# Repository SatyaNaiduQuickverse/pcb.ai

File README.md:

# PCB project starter kit

This repo is the working base for a **Claude-driven PCB design project**, run with a
**master / worker** pair of Claude sessions plus a human project owner.

It is a *starter kit* — it carries the rules, the rigor discipline, the master/worker
protocol, the PCB design-phase structure, and the hard-won lessons from a prior
project. It does **not** yet contain a specific PCB. The project owner briefs the
master on what the board is; the master records it in `CLAUDE.md §2` and the work
begins.

## Read order (cold start)

1. `CLAUDE.md` — the bootstrap: the master/worker model, the rules, the working style.
2. `docs/ENGINEERING_RIGOR.md` — the non-negotiable commitments.
3. `docs/MASTER_WORKER_PROTOCOL.md` — how master and worker communicate + coordinate.
4. `docs/NOVA_COORD_SETUP.md` — deploying this project's coordination server.
5. `docs/DESIGN_PHASES.md` — the PCB design-phase structure (the canonical plan).
6. `docs/PCB_PLAYBOOK.md` — the toolchain + the hard-won routing / manufacturability / sim lessons.

## The model in one line

The **project owner** sets direction. The **master** orchestrates, reviews, gates, and
adjudicates. The **worker** executes the hands-on work (KiCad, sims, builds, fab files).
Master and worker each run as a Claude session; they talk over a small coordination
server. Every phase passes a verification gate before the next begins.

## First steps for a new project

1. Project owner briefs the master on the PCB (function, interfaces, constraints).
2. Master records the project identity + system context in `CLAUDE.md §2` and writes
   a project-specific interface/requirements doc.
3. Master + worker stand up the toolchain and the coordination channel
   (`docs/MASTER_WORKER_PROTOCOL.md`).
4. Work proceeds phase by phase per `docs/DESIGN_PHASES.md`, gated.

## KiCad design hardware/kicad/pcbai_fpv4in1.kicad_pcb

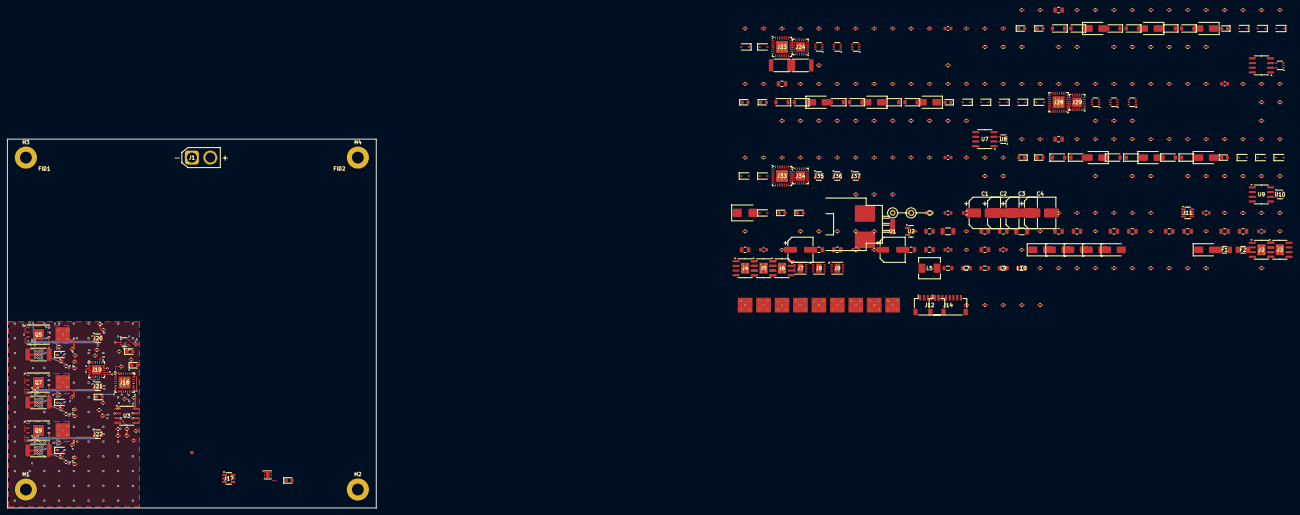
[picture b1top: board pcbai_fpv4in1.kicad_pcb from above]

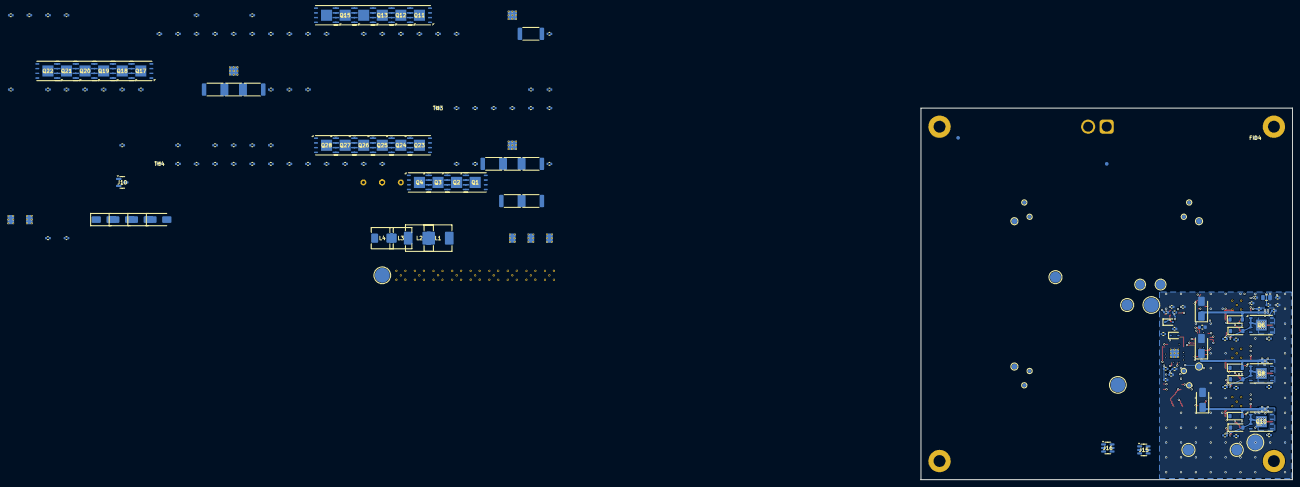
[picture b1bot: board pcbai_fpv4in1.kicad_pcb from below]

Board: 10 copper layers, 100.0 x 100.0 mm, 573 parts (175 on the bottom side), 260 nets.

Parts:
C1, C2, C3, C4: EEHZS1V471P_470uF_35V_polymer; CP_Elec_8x6.2
C5, C9, C13, C16, C19, C53, C83, C113, C143: 10uF; C_0805_2012Metric
C6, C10: 22uF; C_1206_3216Metric
C7, C11, C14, C17, C20, C24, C27, C32, C37, C40, C41, C43, C48, C49, C50, C51, C52, C54, C56, C58, C62, C65, C68, C71, C72, C73, C79, C80, C81, C82, C84, C86, C88, C92, C95, C98, C101, C102, C103, C109, C110, C111, C112, C114, C116, C118, C122, C125, C128, C131, C132, C133, C139, C140, C141, C142, C144, C146, C148, C152, C155, C158, C161, C162, C163, C169, C170: 100nF; C_0402_1005Metric
C8, C12, C15, C18, C21, C22, C25, C29, C30, C34, C35, C38: 22uF; C_0805_2012Metric
C23, C26, C31, C36, C39: 10uF; C_0603_1608Metric
C28, C33: 100uF_6V3_polymer; CP_Elec_6.3x7.7
C42, C45, C46, C47, C55, C57, C59, C60, C61, C85, C87, C89, C90, C91, C115, C117, C119, C120, C121, C145, C147, C149, C150, C151: 1uF; C_0402_1005Metric
C44, C63, C66, C69, C78, C93, C96, C99, C108, C123, C126, C129, C138, C153, C156, C159, C168: 10nF; C_0402_1005Metric
C64, C67, C70, C74, C75, C76, C94, C97, C100, C104, C105, C106, C124, C127, C130, C134, C135, C136, C154, C157, C160, C164, C165, C166: 1nF; C_0402_1005Metric
C77, C107, C137, C167: 22uF; C_0603_1608Metric
D1: SMBJ33A; D_SMB
D2: 12V; D_SOD-323
D3: GREEN_PWR; LED_0603_1608Metric
D4: RED_RPOL; LED_0603_1608Metric
D5, D6, D7, D8, D9: SS54; D_SMA
D10, D11, D12: SMAJ5.0A; D_SMA
D13, D14: SMAJ9.0A; D_SMA
D15, D16, D17, D18: RED_KILL_FW; LED_0603_1608Metric
D19, D20, D21, D22: RED_FAULT_HW; LED_0603_1608Metric
D23: GREEN; LED_0603_1608Metric
D24, D25, D27, D28, D30, D31, D39, D40, D42, D43, D45, D46, D54, D55, D57, D58, D60, D61, D69, D70, D72, D73, D75, D76: BZT52C5V6; D_SOD-123
D26, D29, D32, D41, D44, D47, D56, D59, D62, D71, D74, D77: SMBJ33A; D_SMA
D33, D48, D63, D78: RED; LED_0603_1608Metric
D34, D35, D36, D37, D38, D49, D50, D51, D52, D53, D64, D65, D66, D67, D68, D79, D80, D81, D82, D83: BAT54; D_SOD-323
F1, F2: MF-MSMF200; Fuse_1206_3216Metric
FID1, FID2, FID3, FID4, FID5, FID6: Fiducial_1mm_Mask2mm
H1, H2, H3, H4: MountingHole; MountingHole_3.2mm_M3
J1: BATT_PAD; AMASS_XT30U-M_1x02_P5.0mm_Vertical
J2, J3, J4: TPS54560DDAR; SOIC-8-1EP_3.9x4.9mm_P1.27mm_EP2.29x3mm_ThermalVias
J5, J6: AOZ1284PI; SOIC-8-1EP_3.9x4.9mm_P1.27mm_EP2.29x3mm_ThermalVias
J7, J8, J9: TPS259251DRCR; DFN-10-1EP_3x3mm_P0.5mm_EP1.55x2.48mm
J10: VSUP_5V_TBD; SOT-23
J11: TPS3700_VMOTOR_27V_18V; SOT-23-8
J12: BM06B-SRSS-TB; JST_SH_SM06B-SRSS-TB_1x06-1MP_P1.00mm_Horizontal
J13: TLV76733DRVR; WSON-6-1EP_2x2mm_P0.65mm_EP1x1.6mm
J14: SM08B-SRSS-TB; JST_SH_SM08B-SRSS-TB_1x08-1MP_P1.00mm_Horizontal
J15, J16, J17: USBLC6-2SC6; SOT-23-6
J18, J23, J28, J33: AT32F421K8U7; QFN-32-1EP_5x5mm_P0.5mm_EP3.3x3.3mm_ThermalVias
J19, J24, J29, J34: DRV8300DRGER; HVQFN-24-1EP_4x4mm_P0.5mm_EP2.6x2.6mm
J20, J21, J22, J25, J26, J27, J30, J31, J32, J35, J36, J37: INA186A3IDCKR; SOT-363_SC-70-6
L1, L2: 4.7uH; L_Sunlord_MWSA0605S
L3: 8.2uH; L_Sunlord_MWSA0503S
L4, L5: 10uH; L_Sunlord_MWSA0503S
L6, L7, L8, L9, L10: 600ohm@100MHz; L_0805_2012Metric
L11: 120ohm@100MHz; L_0201_0603Metric
Q1, Q2, Q3, Q4, Q5, Q6, Q7, Q8, Q9, Q10, Q11, Q12, Q13, Q14, Q15, Q16, Q17, Q18, Q19, Q20, Q21, Q22, Q23, Q24, Q25, Q26, Q27, Q28: BSC014N06NS; W-PDFN-8-1EP_6x5mm_P1.27mm_EP3x3mm
R1, R2: MF72_5D25; R_Axial_DIN0207_L6.3mm_D2.5mm_P5.08mm_Vertical
R3: 10K; R_0603_1608Metric
R4, R5: 5K1; R_0603_1608Metric
R6, R8, R10: 52K3; R_0402_1005Metric
R7, R9, R11, R13, R15, R16, R17, R18, R21, R31, R40, R41, R42, R43, R47, R48, R51, R52, R55, R56, R67, R73, R74, R76, R77, R78, R79, R83, R84, R87, R88, R91, R92, R103, R109, R110, R112, R113, R114, R115, R119, R120, R123, R124, R127, R128, R139, R145, R146, R148, R149, R150, R151, R155, R156, R159, R160, R163, R164, R175, R181, R182, R184: 10K; R_0402_1005Metric
R12, R14: 102K; R_0402_1005Metric
R19: 348K; R_0603_1608Metric
R20: 23K2; R_0402_1005Metric
R22, R23, R24, R25, R26, R27, R28, R29, R35, R66, R68, R102, R104, R138, R140, R174, R176: 1K; R_0402_1005Metric
R30: 0R; R_0402_1005Metric
R32, R75, R111, R147, R183: 20K; R_0402_1005Metric
R33, R34: 0R; R_2512_6332Metric
R36, R38, R72, R108, R144, R180: 100K; R_0402_1005Metric
R37: 14K; R_0402_1005Metric
R39: 390R; R_0402_1005Metric
R44, R80, R116, R152: 40K; R_0402_1005Metric
R45, R46, R49, R50, R53, R54, R81, R82, R85, R86, R89, R90, R117, R118, R121, R122, R125, R126, R153, R154, R157, R158, R161, R162: 15R; R_0402_1005Metric
R57, R58, R59, R93, R94, R95, R129, R130, R131, R165, R166, R167: 0.2mR; R_2512_6332Metric
R60, R62, R64, R70, R96, R98, R100, R106, R132, R134, R136, R142, R168, R170, R172, R178: 22K; R_0402_1005Metric
R61, R63, R65, R97, R99, R101, R133, R135, R137, R169, R171, R173: 3.3K; R_0402_1005Metric
R69, R105, R141, R177: 24K; R_0402_1005Metric
R71, R107, R143, R179: 3K; R_0402_1005Metric
TH1, TH2, TH3, TH4: 10K_B4250; R_0402_1005Metric
TP1: PAD_V5_FC_PLUS; TestPoint_Pad_D4.0mm
TP2: PAD_V5_FC_GND; TestPoint_Pad_D4.0mm
TP3: PAD_V5_PI5_PLUS; TestPoint_Pad_D4.0mm
TP5: PAD_V5_AI_PLUS; TestPoint_Pad_D4.0mm
TP7: PAD_V9_VTX1_PLUS; TestPoint_Pad_D3.0mm
TP9: PAD_V9_VTX2_PLUS; TestPoint_Pad_D3.0mm
TP10: PAD_V9_VTX2_GND; TestPoint_Pad_D3.0mm
TP11: PAD_V3V3_PLUS; TestPoint_Pad_D2.5mm
TP12: PAD_V3V3_GND; TestPoint_Pad_D2.5mm
TP16: PAD_GND_DIST_4; TestPoint_Pad_D3.0mm
TP17: BOOT_JUMPER_CH1; TestPoint_Pad_D1.5mm
TP19: MOTOR_A_CH1; ESCMotorPad_4x4mm_5via
TP20: MOTOR_B_CH1; ESCMotorPad_4x4mm_5via
TP21: MOTOR_C_CH1; ESCMotorPad_4x4mm_5via
TP22: SWDIO_CH1; TestPoint_Pad_D1.0mm
TP23: SWCLK_CH1; TestPoint_Pad_D1.0mm
TP24: BOOT_JUMPER_CH2; TestPoint_Pad_D1.5mm
TP26: MOTOR_A_CH2; ESCMotorPad_4x4mm_5via
TP27: MOTOR_B_CH2; ESCMotorPad_4x4mm_5via
TP28: MOTOR_C_CH2; ESCMotorPad_4x4mm_5via
TP29: SWDIO_CH2; TestPoint_Pad_D1.0mm
TP30: SWCLK_CH2; TestPoint_Pad_D1.0mm
TP31: BOOT_JUMPER_CH3; TestPoint_Pad_D1.5mm
TP33: MOTOR_A_CH3; ESCMotorPad_4x4mm_5via
TP34: MOTOR_B_CH3; ESCMotorPad_4x4mm_5via
TP35: MOTOR_C_CH3; ESCMotorPad_4x4mm_5via
TP36: SWDIO_CH3; TestPoint_Pad_D1.0mm
TP37: SWCLK_CH3; TestPoint_Pad_D1.0mm
TP38: BOOT_JUMPER_CH4; TestPoint_Pad_D1.5mm
TP40: MOTOR_A_CH4; ESCMotorPad_4x4mm_5via
TP41: MOTOR_B_CH4; ESCMotorPad_4x4mm_5via
TP42: MOTOR_C_CH4; ESCMotorPad_4x4mm_5via
TP43: SWDIO_CH4; TestPoint_Pad_D1.0mm
TP44: SWCLK_CH4; TestPoint_Pad_D1.0mm
U1: ACS770ECB-200B-PFF-T; Allegro_CB_PFF
U2: TL431LI; SOT-23
U3, U5, U7, U9: LM393; SOIC-8_3.9x4.9mm_P1.27mm
U4, U6, U8, U10: 74LVC1G08; SOT-353_SC-70-5

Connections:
+3V3: C46.1, C51.1, C52.1, C53.1, C79.1, C80.1, C81.1, C82.1, C83.1, C109.1, C110.1, C111.1, C112.1, C113.1, C139.1, C140.1, C141.1, C142.1, C143.1, C169.1, C170.1, J11.1, J11.7, J11.8, J12.2, J13.5, J18.1, J18.17, J20.4, J21.4, J22.4, J23.1, J23.17, J25.4, J26.4, J27.4, J28.1, J28.17, J30.4, J31.4, J32.4, J33.1, J33.17, J35.4, J36.4, J37.4, L11.1, R21.2, R22.1, R23.1, R24.1, R25.1, R26.1, R27.1, R28.1, R29.1, R35.1, R39.1, R40.2, R42.2, R66.1, R67.1, R73.2, R74.2, R76.2, R78.2, R102.1, R103.1, R109.2, R110.2, R112.2, R114.2, R138.1, R139.1, R145.2, R146.2, R148.2, R150.2, R174.1, R175.1, R181.2, R182.2, R184.2, TP11.1, U3.8, U4.5, U5.8, U6.5, U7.8, U8.5, U9.8, U10.5
+3V3A: C47.1, C48.1, C54.1, C55.1, C84.1, C85.1, C114.1, C115.1, C144.1, C145.1, J18.5, J23.5, J28.5, J33.5, L11.2
+BATT: J1.1, R1.1, R2.1, R5.1, R36.1
+V5_AI: C30.1, C31.1, C32.1, C33.1, C34.1, L8.2, TP5.1
+V5_FC: C22.1, C23.1, C24.1, C45.1, C57.1, C58.1, C77.1, C87.1, C88.1, C107.1, C117.1, C118.1, C137.1, C147.1, C148.1, C167.1, J13.1, J13.3, J15.3, J16.3, J17.3, J19.4, J24.4, J29.4, J34.4, L6.2, R30.1, TP1.1
+V5_PI5: C25.1, C26.1, C27.1, C28.1, C29.1, J10.1, L7.2, TP3.1
+V9_VTX1: C35.1, C36.1, C37.1, L9.2, TP7.1
+V9_VTX2: C38.1, C39.1, C40.1, L10.2, TP9.1
+VMOTOR: C1.1, C2.1, C3.1, C4.1, C5.1, C6.1, C9.1, C10.1, C13.1, C16.1, C19.1, D1.2, J2.2, J2.3, J3.2, J3.3, J4.2, J4.3, J5.2, J5.3, J6.2, J6.3, R1.2, R2.2, R3.1, R4.1, R19.1, R33.1
BATGND: D4.1, J1.2, Q1.1, Q1.2, Q1.3, Q1.9, Q2.1, Q2.2, Q2.3, Q2.9, Q3.1, Q3.2, Q3.3, Q3.9, Q4.1, Q4.2, Q4.3, Q4.9
BEMF_A_CH1: C74.1, J18.6, R60.2, R61.1
BEMF_A_CH2: C104.1, J23.6, R96.2, R97.1
BEMF_A_CH3: C134.1, J28.6, R132.2, R133.1
BEMF_A_CH4: C164.1, J33.6, R168.2, R169.1
BEMF_B_CH1: C75.1, J18.10, R62.2, R63.1
BEMF_B_CH2: C105.1, J23.10, R98.2, R99.1
BEMF_B_CH3: C135.1, J28.10, R134.2, R135.1
BEMF_B_CH4: C165.1, J33.10, R170.2, R171.1
BEMF_C_CH1: C76.1, J18.11, R64.2, R65.1
BEMF_C_CH2: C106.1, J23.11, R100.2, R101.1
BEMF_C_CH3: C136.1, J28.11, R136.2, R137.1
BEMF_C_CH4: C166.1, J33.11, R172.2, R173.1
BOOT0_CH1: J18.31, R41.1, R43.1, TP17.1
BOOT0_CH2: J23.31, R77.1, R79.1, TP24.1
BOOT0_CH3: J28.31, R113.1, R115.1, TP31.1
BOOT0_CH4: J33.31, R149.1, R151.1, TP38.1
BSTA_CH1: C59.1, J19.20
BSTA_CH2: C89.1, J24.20
BSTA_CH3: C119.1, J29.20
BSTA_CH4: C149.1, J34.20
BSTB_CH1: C60.1, J19.17
BSTB_CH2: C90.1, J24.17
BSTB_CH3: C120.1, J29.17
BSTB_CH4: C150.1, J34.17
BSTC_CH1: C61.1, J19.14
BSTC_CH2: C91.1, J24.14
BSTC_CH3: C121.1, J29.14
BSTC_CH4: C151.1, J34.14
BUCK1_BST: C7.1, J2.1
BUCK1_FB: J2.4, R6.2, R7.1
BUCK1_SW: C7.2, D5.2, J2.6, J2.7, L1.1
BUCK2_BST: C11.1, J3.1
BUCK2_FB: J3.4, R8.2, R9.1
BUCK2_SW: C11.2, D6.2, J3.6, J3.7, L2.1
BUCK3_BST: C14.1, J4.1
BUCK3_FB: J4.4, R10.2, R11.1
BUCK3_SW: C14.2, D7.2, J4.6, J4.7, L3.1
BUCK4_BST: C17.1, J5.1
BUCK4_FB: J5.4, R12.2, R13.1
BUCK4_SW: C17.2, D8.2, J5.6, J5.7, L4.1
BUCK5_BST: C20.1, J6.1
BUCK5_FB: J6.4, R14.2, R15.1
BUCK5_SW: C20.2, D9.2, J6.6, J6.7, L5.1
BUS_CURR_HALL_OUT: C44.1, J12.3, R31.2, R32.1
CSA_A_OUT_CH1: C71.1, D34.2, J18.8, J20.5
CSA_A_OUT_CH2: C101.1, D49.2, J23.8, J25.5
CSA_A_OUT_CH3: C131.1, D64.2, J28.8, J30.5
CSA_A_OUT_CH4: C161.1, D79.2, J33.8, J35.5
CSA_B_OUT_CH1: C72.1, D35.2, J21.5
CSA_B_OUT_CH2: C102.1, D50.2, J26.5
CSA_B_OUT_CH3: C132.1, D65.2, J31.5
CSA_B_OUT_CH4: C162.1, D80.2, J36.5
CSA_C_OUT_CH1: C73.1, D36.2, J22.5
CSA_C_OUT_CH2: C103.1, D51.2, J27.5
CSA_C_OUT_CH3: C133.1, D66.2, J32.5
CSA_C_OUT_CH4: C163.1, D81.2, J37.5
CSA_MAX_CH1: D34.1, D35.1, D36.1, R72.1, U3.2
CSA_MAX_CH2: D49.1, D50.1, D51.1, R108.1, U5.2
CSA_MAX_CH3: D64.1, D65.1, D66.1, R144.1, U7.2
CSA_MAX_CH4: D79.1, D80.1, D81.1, R180.1, U9.2
CURR_OUT: J14.3, R38.1
GATE_RP: D2.1, Q1.4, Q2.4, Q3.4, Q4.4, R3.2
GHA_CH1: J19.19, R45.1
GHA_CH2: J24.19, R81.1
GHA_CH3: J29.19, R117.1
GHA_CH4: J34.19, R153.1
GHB_CH1: J19.16, R49.1
GHB_CH2: J24.16, R85.1
GHB_CH3: J29.16, R121.1
GHB_CH4: J34.16, R157.1
GHC_CH1: J19.13, R53.1
GHC_CH2: J24.13, R89.1
GHC_CH3: J29.13, R125.1
GHC_CH4: J34.13, R161.1
GLA_CH1: J19.11, R46.1
GLA_CH2: J24.11, R82.1
GLA_CH3: J29.11, R118.1
GLA_CH4: J34.11, R154.1
GLB_CH1: J19.10, R50.1
GLB_CH2: J24.10, R86.1
GLB_CH3: J29.10, R122.1
GLB_CH4: J34.10, R158.1
GLC_CH1: J19.9, R54.1
GLC_CH2: J24.9, R90.1
GLC_CH3: J29.9, R126.1
GLC_CH4: J34.9, R162.1
GND: C1.2, C2.2, C3.2, C4.2, C5.2, C6.2, C8.2, C9.2, C10.2, C12.2, C13.2, C15.2, C16.2, C18.2, C19.2, C21.2, C22.2, C23.2, C24.2, C25.2, C26.2, C27.2, C28.2, C29.2, C30.2, C31.2, C32.2, C33.2, C34.2, C35.2, C36.2, C37.2, C38.2, C39.2, C40.2, C41.2, C42.2, C43.2, C44.2, C45.2, C46.2, C47.2, C48.2, C49.2, C50.2, C51.2, C52.2, C53.2, C54.2, C55.2, C56.2, C57.2, C58.2, C62.2, C63.2, C64.2, C65.2, C66.2, C67.2, C68.2, C69.2, C70.2, C71.2, C72.2, C73.2, C74.2, C75.2, C76.2, C77.2, C78.2, C79.2, C80.2, C81.2, C82.2, C83.2, C84.2, C85.2, C86.2, C87.2, C88.2, C92.2, C93.2, C94.2, C95.2, C96.2, C97.2, C98.2, C99.2, C100.2, C101.2, C102.2, C103.2, C104.2, C105.2, C106.2, C107.2, C108.2, C109.2, C110.2, C111.2, C112.2, C113.2, C114.2, C115.2, C116.2, C117.2, C118.2, C122.2, C123.2, C124.2, C125.2, C126.2, C127.2, C128.2, C129.2, C130.2, C131.2, C132.2, C133.2, C134.2, C135.2, C136.2, C137.2, C138.2, C139.2, C140.2, C141.2, C142.2, C143.2, C144.2, C145.2, C146.2, C147.2, C148.2, C152.2, C153.2, C154.2, C155.2, C156.2, C157.2, C158.2, C159.2, C160.2, C161.2, C162.2, C163.2, C164.2, C165.2, C166.2, C167.2, C168.2, C169.2, C170.2, D1.1, D2.2, D3.1, D5.1, D6.1, D7.1, D8.1, D9.1, D10.1, D11.1, D12.1, D13.1, D14.1, D23.1, D26.2, D29.2, D32.2, D41.2, D44.2, D47.2, D56.2, D59.2, D62.2, D71.2, D74.2, D77.2, J2.5, J2.8, J3.5, J3.8, J4.5, J4.8, J5.5, J5.8, J6.5, J6.8, J7.3, J8.3, J9.3, J10.2, J11.2, J12.1, J13.2, J14.1, J15.2, J15.5, J16.2, J16.5, J17.2, J17.5, J18.7, J18.16, J18.32, J19.5, J19.6, J20.2, J20.3, J20.6, J21.2, J21.3, J21.6, J22.2, J22.3, J22.6, J23.7, J23.16, J23.32, J24.5, J24.6, J25.2, J25.3, J25.6, J26.2, J26.3, J26.6, J27.2, J27.3, J27.6, J28.7, J28.16, J28.32, J29.5, J29.6, J30.2, J30.3, J30.6, J31.2, J31.3, J31.6, J32.2, J32.3, J32.6, J33.7, J33.16, J33.32, J34.5, J34.6, J35.2, J35.3, J35.6, J36.2, J36.3, J36.6, J37.2, J37.3, J37.6, Q1.5, Q1.6, Q1.7, Q1.8, Q2.5, Q2.6, Q2.7, Q2.8, Q3.5, Q3.6, Q3.7, Q3.8, Q4.5, Q4.6, Q4.7, Q4.8, R7.2, R9.2, R11.2, R13.2, R15.2, R16.2, R17.2, R18.2, R20.2, R32.2, R37.2, R38.2, R41.2, R43.2, R44.2, R57.2, R58.2, R59.2, R61.2, R63.2, R65.2, R69.2, R71.2, R72.2, R77.2, R79.2, R80.2, R93.2, R94.2, R95.2, R97.2, R99.2, R101.2, R105.2, R107.2, R108.2, R113.2, R115.2, R116.2, R129.2, R130.2, R131.2, R133.2, R135.2, R137.2, R141.2, R143.2, R144.2, R149.2, R151.2, R152.2, R165.2, R166.2, R167.2, R169.2, R171.2, R173.2, R177.2, R179.2, R180.2, TH1.2, TH2.2, TH3.2, TH4.2, TP2.1, TP10.1, TP12.1, TP16.1, U1.2, U2.3, U3.4, U4.3, U5.4, U6.3, U7.4, U8.3, U9.4, U10.3
HALL_VCC_5V: C42.1, C43.1, R30.2, U1.1
HALL_VOUT_RAW: R31.1, U1.3
HW_FAULT_LED_K_CH2: D20.1, D53.1, U6.4
HW_FAULT_LED_K_CH4: D22.1, D83.1, U10.4
I_TRIP_N_CH1: R73.1, R75.1, U3.1, U4.1
I_TRIP_N_CH2: R109.1, R111.1, U5.1, U6.1
I_TRIP_N_CH3: R145.1, R147.1, U7.1, U8.1
I_TRIP_N_CH4: R181.1, R183.1, U9.1, U10.1
KILL_LED_NODE_CH1: D15.2, R22.2
KILL_LED_NODE_CH2: D16.2, R23.2
KILL_LED_NODE_CH3: D17.2, R24.2
KILL_LED_NODE_CH4: D18.2, R25.2
KILL_LOCAL_N_CH1: D19.1, D38.1, U4.4
KILL_LOCAL_N_CH3: D21.1, D68.1, U8.4
KILL_RAIL_N_CH1: D37.2, D38.2, J19.8, R76.1
KILL_RAIL_N_CH2: D52.2, D53.2, J24.8, R112.1
KILL_RAIL_N_CH3: D67.2, D68.2, J29.8, R148.1
KILL_RAIL_N_CH4: D82.2, D83.2, J34.8, R184.1
LED_GPIO_CH1: D33.1, J18.25
LED_GPIO_CH2: D48.1, J23.25
LED_GPIO_CH3: D63.1, J28.25
LED_GPIO_CH4: D78.1, J33.25
LED_PG_NODE: D23.2, R35.2
LED_PWR_NODE: D3.2, R4.2
LED_RPOL_NODE: D4.2, R5.2
M1_CLEAN: J14.8, J15.1, J15.6, J18.27
M2_RAW: J14.7, J15.4, J23.27
M3_CLEAN: J14.6, J16.1, J16.6, J28.27
M4_RAW: J14.5, J16.4, J33.27
MOTOR_A_CH1: C59.2, D24.2, D26.1, J19.18, Q5.1, Q5.2, Q5.3, Q5.9, Q6.5, Q6.6, Q6.7, Q6.8, R47.2, R60.1, TP19.1
MOTOR_A_CH2: C89.2, D39.2, D41.1, J24.18, Q11.1, Q11.2, Q11.3, Q11.9, Q12.5, Q12.6, Q12.7, Q12.8, R83.2, R96.1, TP26.1
MOTOR_A_CH3: C119.2, D54.2, D56.1, J29.18, Q17.1, Q17.2, Q17.3, Q17.9, Q18.5, Q18.6, Q18.7, Q18.8, R119.2, R132.1, TP33.1
MOTOR_A_CH4: C149.2, D69.2, D71.1, J34.18, Q23.1, Q23.2, Q23.3, Q23.9, Q24.5, Q24.6, Q24.7, Q24.8, R155.2, R168.1, TP40.1
MOTOR_B_CH1: C60.2, D27.2, D29.1, J19.15, Q7.1, Q7.2, Q7.3, Q7.9, Q8.5, Q8.6, Q8.7, Q8.8, R51.2, R62.1, TP20.1
MOTOR_B_CH2: C90.2, D42.2, D44.1, J24.15, Q13.1, Q13.2, Q13.3, Q13.9, Q14.5, Q14.6, Q14.7, Q14.8, R87.2, R98.1, TP27.1
MOTOR_B_CH3: C120.2, D57.2, D59.1, J29.15, Q19.1, Q19.2, Q19.3, Q19.9, Q20.5, Q20.6, Q20.7, Q20.8, R123.2, R134.1, TP34.1
MOTOR_B_CH4: C150.2, D72.2, D74.1, J34.15, Q25.1, Q25.2, Q25.3, Q25.9, Q26.5, Q26.6, Q26.7, Q26.8, R159.2, R170.1, TP41.1
MOTOR_C_CH1: C61.2, D30.2, D32.1, J19.12, Q9.1, Q9.2, Q9.3, Q9.9, Q10.5, Q10.6, Q10.7, Q10.8, R55.2, R64.1, TP21.1
MOTOR_C_CH2: C91.2, D45.2, D47.1, J24.12, Q15.1, Q15.2, Q15.3, Q15.9, Q16.5, Q16.6, Q16.7, Q16.8, R91.2, R100.1, TP28.1
MOTOR_C_CH3: C121.2, D60.2, D62.1, J29.12, Q21.1, Q21.2, Q21.3, Q21.9, Q22.5, Q22.6, Q22.7, Q22.8, R127.2, R136.1, TP35.1
MOTOR_C_CH4: C151.2, D75.2, D77.1, J34.12, Q27.1, Q27.2, Q27.3, Q27.9, Q28.5, Q28.6, Q28.7, Q28.8, R163.2, R172.1, TP42.1
unnamed: J7.5, R16.1
unnamed: J8.5, R17.1
unnamed: J9.5, R18.1
unnamed: D19.2, R26.2
unnamed: D20.2, R27.2
unnamed: D21.2, R28.2
unnamed: D22.2, R29.2
unnamed: J19.21, R44.1
unnamed: D24.1, Q5.4, R45.2, R47.1
unnamed: D25.1, Q6.4, R46.2, R48.1
unnamed: D27.1, Q7.4, R49.2, R51.1
unnamed: D28.1, Q8.4, R50.2, R52.1
unnamed: D30.1, Q9.4, R53.2, R55.1
unnamed: D31.1, Q10.4, R54.2, R56.1
unnamed: D33.2, R66.2
unnamed: J24.21, R80.1
unnamed: D39.1, Q11.4, R81.2, R83.1
unnamed: D40.1, Q12.4, R82.2, R84.1
unnamed: D42.1, Q13.4, R85.2, R87.1
unnamed: D43.1, Q14.4, R86.2, R88.1
unnamed: D45.1, Q15.4, R89.2, R91.1
unnamed: D46.1, Q16.4, R90.2, R92.1
unnamed: D48.2, R102.2
unnamed: J29.21, R116.1
unnamed: D54.1, Q17.4, R117.2, R119.1
unnamed: D55.1, Q18.4, R118.2, R120.1
unnamed: D57.1, Q19.4, R121.2, R123.1
unnamed: D58.1, Q20.4, R122.2, R124.1
unnamed: D60.1, Q21.4, R125.2, R127.1
unnamed: D61.1, Q22.4, R126.2, R128.1
unnamed: D63.2, R138.2
unnamed: J34.21, R152.1
unnamed: D69.1, Q23.4, R153.2, R155.1
unnamed: D70.1, Q24.4, R154.2, R156.1
unnamed: D72.1, Q25.4, R157.2, R159.1
unnamed: D73.1, Q26.4, R158.2, R160.1
unnamed: D75.1, Q27.4, R161.2, R163.1
unnamed: D76.1, Q28.4, R162.2, R164.1
unnamed: D78.2, R174.2
NRST_CH1: C56.1, J18.4, R42.1
NRST_CH2: C86.1, J23.4, R78.1
NRST_CH3: C116.1, J28.4, R114.1
NRST_CH4: C146.1, J33.4, R150.1
NTC_CH1_1: R67.2, TH1.1, U3.5
NTC_CH2_1: R103.2, TH2.1, U5.5
NTC_CH3_1: R139.2, TH3.1, U7.5
NTC_CH4_1: R175.2, TH4.1, U9.5
OTP_TRIP_N_CH1: R74.1, U3.7, U4.2
OTP_TRIP_N_CH2: R110.1, U5.7, U6.2
OTP_TRIP_N_CH3: R146.1, U7.7, U8.2
OTP_TRIP_N_CH4: R182.1, U9.7, U10.2
PG_VMOTOR: D37.1, D52.1, D67.1, D82.1, J11.5, R21.1
PWM_INHA_CH1: J18.20, J19.22
PWM_INHA_CH2: J23.20, J24.22
PWM_INHA_CH3: J28.20, J29.22
PWM_INHA_CH4: J33.20, J34.22
PWM_INHB_CH1: J18.19, J19.23
PWM_INHB_CH2: J23.19, J24.23
PWM_INHB_CH3: J28.19, J29.23
PWM_INHB_CH4: J33.19, J34.23
PWM_INHC_CH1: J18.18, J19.24
PWM_INHC_CH2: J23.18, J24.24
PWM_INHC_CH3: J28.18, J29.24
PWM_INHC_CH4: J33.18, J34.24
PWM_INLA_CH1: J18.15, J19.1
PWM_INLA_CH2: J23.15, J24.1
PWM_INLA_CH3: J28.15, J29.1
PWM_INLA_CH4: J33.15, J34.1
PWM_INLB_CH1: J18.14, J19.2
PWM_INLB_CH2: J23.14, J24.2
PWM_INLB_CH3: J28.14, J29.2
PWM_INLB_CH4: J33.14, J34.2
PWM_INLC_CH1: J18.13, J19.3
PWM_INLC_CH2: J23.13, J24.3
PWM_INLC_CH3: J28.13, J29.3
PWM_INLC_CH4: J33.13, J34.3
SHUNT_A_TOP_CH1: D25.2, J20.1, Q6.1, Q6.2, Q6.3, Q6.9, R48.2, R57.1
SHUNT_A_TOP_CH2: D40.2, J25.1, Q12.1, Q12.2, Q12.3, Q12.9, R84.2, R93.1
SHUNT_A_TOP_CH3: D55.2, J30.1, Q18.1, Q18.2, Q18.3, Q18.9, R120.2, R129.1
SHUNT_A_TOP_CH4: D70.2, J35.1, Q24.1, Q24.2, Q24.3, Q24.9, R156.2, R165.1
SHUNT_B_TOP_CH1: D28.2, J21.1, Q8.1, Q8.2, Q8.3, Q8.9, R52.2, R58.1
SHUNT_B_TOP_CH2: D43.2, J26.1, Q14.1, Q14.2, Q14.3, Q14.9, R88.2, R94.1
SHUNT_B_TOP_CH3: D58.2, J31.1, Q20.1, Q20.2, Q20.3, Q20.9, R124.2, R130.1
SHUNT_B_TOP_CH4: D73.2, J36.1, Q26.1, Q26.2, Q26.3, Q26.9, R160.2, R166.1
SHUNT_C_TOP_CH1: D31.2, J22.1, Q10.1, Q10.2, Q10.3, Q10.9, R56.2, R59.1
SHUNT_C_TOP_CH2: D46.2, J27.1, Q16.1, Q16.2, Q16.3, Q16.9, R92.2, R95.1
SHUNT_C_TOP_CH3: D61.2, J32.1, Q22.1, Q22.2, Q22.3, Q22.9, R128.2, R131.1
SHUNT_C_TOP_CH4: D76.2, J37.1, Q28.1, Q28.2, Q28.3, Q28.9, R164.2, R167.1
SWCLK_CH1: J18.24, TP23.1
SWCLK_CH2: J23.24, TP30.1
SWCLK_CH3: J28.24, TP37.1
SWCLK_CH4: J33.24, TP44.1
SWDIO_CH1: J18.23, TP22.1
SWDIO_CH2: J23.23, TP29.1
SWDIO_CH3: J28.23, TP36.1
SWDIO_CH4: J33.23, TP43.1
TLM: J14.4, J17.1, J17.6, J18.29, J23.29, J28.29, J33.29, R40.1
V5_AI_PROTECT_OUT: D12.2, J9.8, J9.9, L8.1
V5_FC_PROTECT_OUT: D10.2, J7.8, J7.9, L6.1
V5_PI5_PROTECT_OUT: D11.2, J8.8, J8.9, L7.1
V9_VTX1_PROTECT_OUT: D13.2, F1.2, L9.1
V9_VTX2_PROTECT_OUT: D14.2, F2.2, L10.1
VBAT_SENSE_OUT: C49.1, J14.2, R36.2, R37.1
VMOTOR_CH: C62.1, C63.1, C64.1, C65.1, C66.1, C67.1, C68.1, C69.1, C70.1, C92.1, C93.1, C94.1, C95.1, C96.1, C97.1, C98.1, C99.1, C100.1, C122.1, C123.1, C124.1, C125.1, C126.1, C127.1, C128.1, C129.1, C130.1, C152.1, C153.1, C154.1, C155.1, C156.1, C157.1, C158.1, C159.1, C160.1, Q5.5, Q5.6, Q5.7, Q5.8, Q7.5, Q7.6, Q7.7, Q7.8, Q9.5, Q9.6, Q9.7, Q9.8, Q11.5, Q11.6, Q11.7, Q11.8, Q13.5, Q13.6, Q13.7, Q13.8, Q15.5, Q15.6, Q15.7, Q15.8, Q17.5, Q17.6, Q17.7, Q17.8, Q19.5, Q19.6, Q19.7, Q19.8, Q21.5, Q21.6, Q21.7, Q21.8, Q23.5, Q23.6, Q23.7, Q23.8, Q25.5, Q25.6, Q25.7, Q25.8, Q27.5, Q27.6, Q27.7, Q27.8, R34.2
VMOTOR_DIV: J11.3, J11.4, R19.2, R20.1
VMOTOR_HALL_HI: R33.2, U1.4
VMOTOR_HALL_LO: R34.1, U1.5
VMOTOR_SUPER_CT: C41.1, J11.6
VREF_2V5: C50.1, C78.1, C108.1, C138.1, C168.1, R39.2, R68.1, R70.1, R104.1, R106.1, R140.1, R142.1, R176.1, R178.1, U2.1, U2.2
VREF_I_TRIP_CH1: R68.2, R69.1, R75.2, U3.3
VREF_I_TRIP_CH2: R104.2, R105.1, R111.2, U5.3
VREF_I_TRIP_CH3: R140.2, R141.1, R147.2, U7.3
VREF_I_TRIP_CH4: R176.2, R177.1, R183.2, U9.3
VREF_OTP_CH1: R70.2, R71.1, U3.6
VREF_OTP_CH2: R106.2, R107.1, U5.6
VREF_OTP_CH3: R142.2, R143.1, U7.6
VREF_OTP_CH4: R178.2, R179.1, U9.6
V_BUCK1_OUT: C8.1, J7.1, J7.2, J7.4, L1.2, R6.1
V_BUCK2_OUT: C12.1, J8.1, J8.2, J8.4, L2.2, R8.1
V_BUCK3_OUT: C15.1, J9.1, J9.2, J9.4, L3.2, R10.1
V_BUCK4_OUT: C18.1, F1.1, L4.2, R12.1
V_BUCK5_OUT: C21.1, F2.1, L5.2, R14.1

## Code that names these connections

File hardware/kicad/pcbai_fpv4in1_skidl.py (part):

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U_VMOTOR_SUPER[3] += VMOTOR_DIV      # INA (upper threshold input)
U_VMOTOR_SUPER[4] += VMOTOR_DIV      # INB (lower threshold input)
U_VMOTOR_SUPER[5] += PG_VMOTOR       # SENSE_RESET (open-drain fault flag)
U_VMOTOR_SUPER[6] += Net("VMOTOR_SUPER_CT")  # CT delay cap pin
U_VMOTOR_SUPER[7] += V3V3            # ENABLE (tied high — always-on)
U_VMOTOR_SUPER[8] += V3V3            # NC / spare

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# data — bus saturation event is detectable from FC's per-motor sum vs bus.
HALL_VCC = Net("HALL_VCC_5V")            # 5V supply for ACS770 (V5 rail)
HALL_VOUT_RAW = Net("HALL_VOUT_RAW")     # 5V-domain ratiometric output
BUS_CURR_HALL_OUT = Net("BUS_CURR_HALL_OUT")  # AUX header pin 3 (to FC)
VMOTOR_HALL_HI = Net("VMOTOR_HALL_HI")   # primary side IN (from CBULK output side)
VMOTOR_HALL_LO = Net("VMOTOR_HALL_LO")   # primary side OUT (to 4-channel split)

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
# ─────────── CURR_OUT decision (Phase 3c — closes 3a deferred item) ──────────
# Master directive verified vs Betaflight 4-in-1 8-pin standard:
#   The TLM (telemetry) single-wire UART (pin 4) carries per-channel current
#   data reported by AM32 firmware (USE_SERIAL_TELEMETRY=yes per target.h
#   Phase 2c lock). FC parses this via the "Esc_sensor" / "Telemetry" data
#   stream. Analog CURR_OUT is NOT part of Betaflight's 4-in-1 standard.
#
# Decision: NO analog CURR aggregation hardware. The FC connector pin 3
# (defined as CURR_OUT in Phase 3a) is left as a future-expansion pin (e.g.,
# could carry RPM signal or auxiliary analog). For now, tie CURR_OUT to GND
# through a 100 kΩ pull-down to provide a defined inactive level (so the
# FC's analog input doesn't float when this ESC is connected; a floating
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
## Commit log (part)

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2026-05-28 [methodology-change] Re-lock ROUTING_TOPOLOGY_HASH post PR #239 (drift gate fix)
